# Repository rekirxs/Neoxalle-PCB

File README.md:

# NeoXalle-PCB

A full PCB work for a sport sensorial reaction device called NeoXalle.

The function of this pcb is to be the main board to control the whole system of the multisensorial output and input, such as a motor vibrator and led ring, this includes a Esp32c3 to connect thru ESP-NOW to the master that connects to the mobile app, down below theres a video showing off the prototype and its function with a table tennis practice.

**Overview**

This repository contains the design files and the images of each part.

### [Watch this video on YouTube](https://youtu.be/leAVq9ZJ1fE)
**Screenshots**

Onshape: https://cad.onshape.com/documents/914ab1e3f9de5857bd04cad5/w/fe3775e11ed4b5ce7c2d1721/e/2a4a9405b78e8a972a361091?renderMode=0&uiState=6a0a02086fff7314551b3a2c

|Item                        |Description                        |Quantity|Unit Price ($)|Total Price ($)|URL                                                 |Running Total|
|----------------------------|-----------------------------------|--------|--------------|---------------|----------------------------------------------------|-------------|
|ESP32-C3 Super Mini         |Microcontroller                    |1       |3.48          |3.48           |https://es.aliexpress.com/item/1005007941259180.html|3.48         |
|MPU6050                     | Acelerometer                      |1       |2.47          |2.47           |https://es.aliexpress.com/item/1005008796700745.html|5.95         |
|Pogo Pins                   |4 pin 360 Degree Magnetic Pogo Pins|1       |4.3           |4.3            |https://es.aliexpress.com/item/1005007457425590.html|10.25        |
|1200mAh battery             |Battery                            |1       |24.59         |24.59          |https://es.aliexpress.com/item/1005011601135401.html|34.84        |
|Coin Vibrator Motor         |Vibrator Motor                     |1       |1.22          |1.22           |https://es.aliexpress.com/item/1005006713206227.html|36.06        |
|24x LED Ring WS2812b        |LED Ring                           |1       |2.24          |2.24           |https://es.aliexpress.com/item/1005009290613680.html|38.3         |
|12v-5v Buck Converter       |Buck Converter                     |1       |3.04          |3.04           |https://es.aliexpress.com/item/1005008257960729.html|41.34        |
|2n39004 Transistor          |Transistor                         |1       |4.1           |4.1            |https://es.aliexpress.com/item/1005004029392929.html|45.44        |
|1N4007 Diode                |Schockty Diode                     |1       |1.75          |1.75           |https://es.aliexpress.com/item/1005007807556976.html|47.19        |
|680ohm resistor             |Resistor                           |1       |1.33          |1.33           |https://es.aliexpress.com/item/32847423196.html     |48.52        |
|AMS1117                     |Voltage Reductor                   |1       |1.34          |1.34           |https://es.aliexpress.com/item/4001091314348.html   |49.86        |
|USB-C Battery Charger Module|Battery Charger Module             |1       |1.1           |1.1            |https://es.aliexpress.com/item/1005006161180492.html|50.96        |

**Repository layout**
- `cad/` — CAD files and case models
- `pcb/` — KiCad schematic and PCB files- `firmware/` — KMK firmware and `keymap.py`
- `images/` — project screenshots used by this README

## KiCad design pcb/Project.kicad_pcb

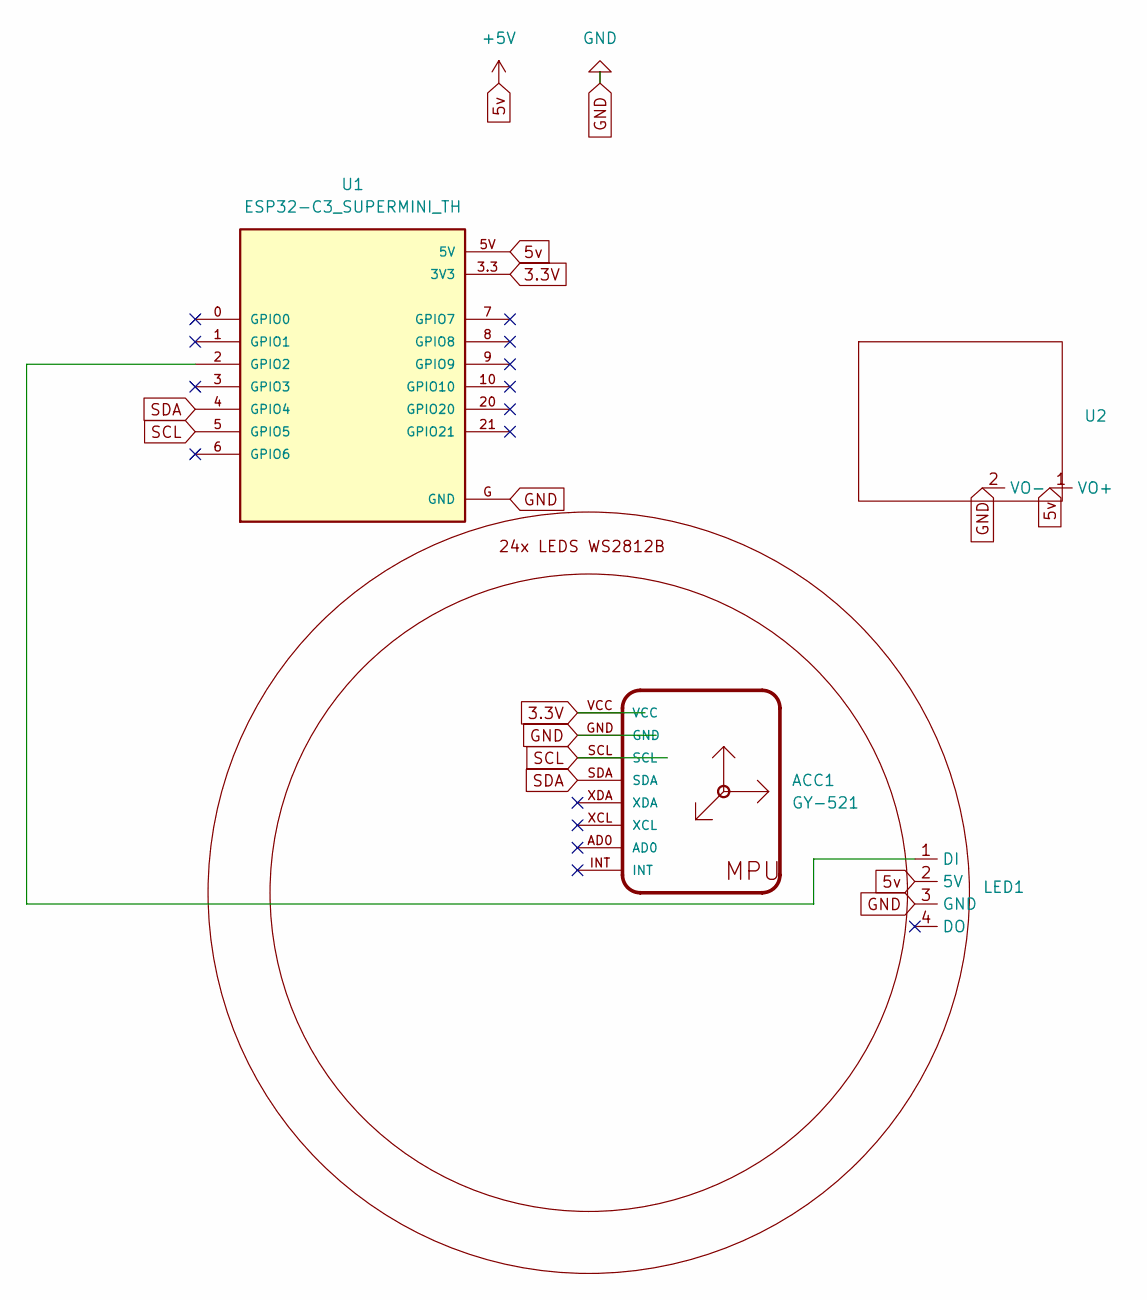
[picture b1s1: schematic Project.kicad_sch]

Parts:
ACC1: GY-521
LED1: Untitled
U1: ESP32-C3_SUPERMINI_TH; MODULE_ESP32-C3_SUPERMINI_TH
U2: ModuleCharger

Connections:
3.3V: ACC1.VCC, U1.3.3 (3V3)
5v: LED1.2 (5V), U1.5V, U2.1 (VO+)
GND: ACC1.GND, LED1.3 (GND), U1.G (GND), U2.2 (VO-)
unnamed: LED1.1 (DI), U1.2 (GPIO2)
SCL: ACC1.SCL, U1.5 (GPIO5)
SDA: ACC1.SDA, U1.4 (GPIO4)

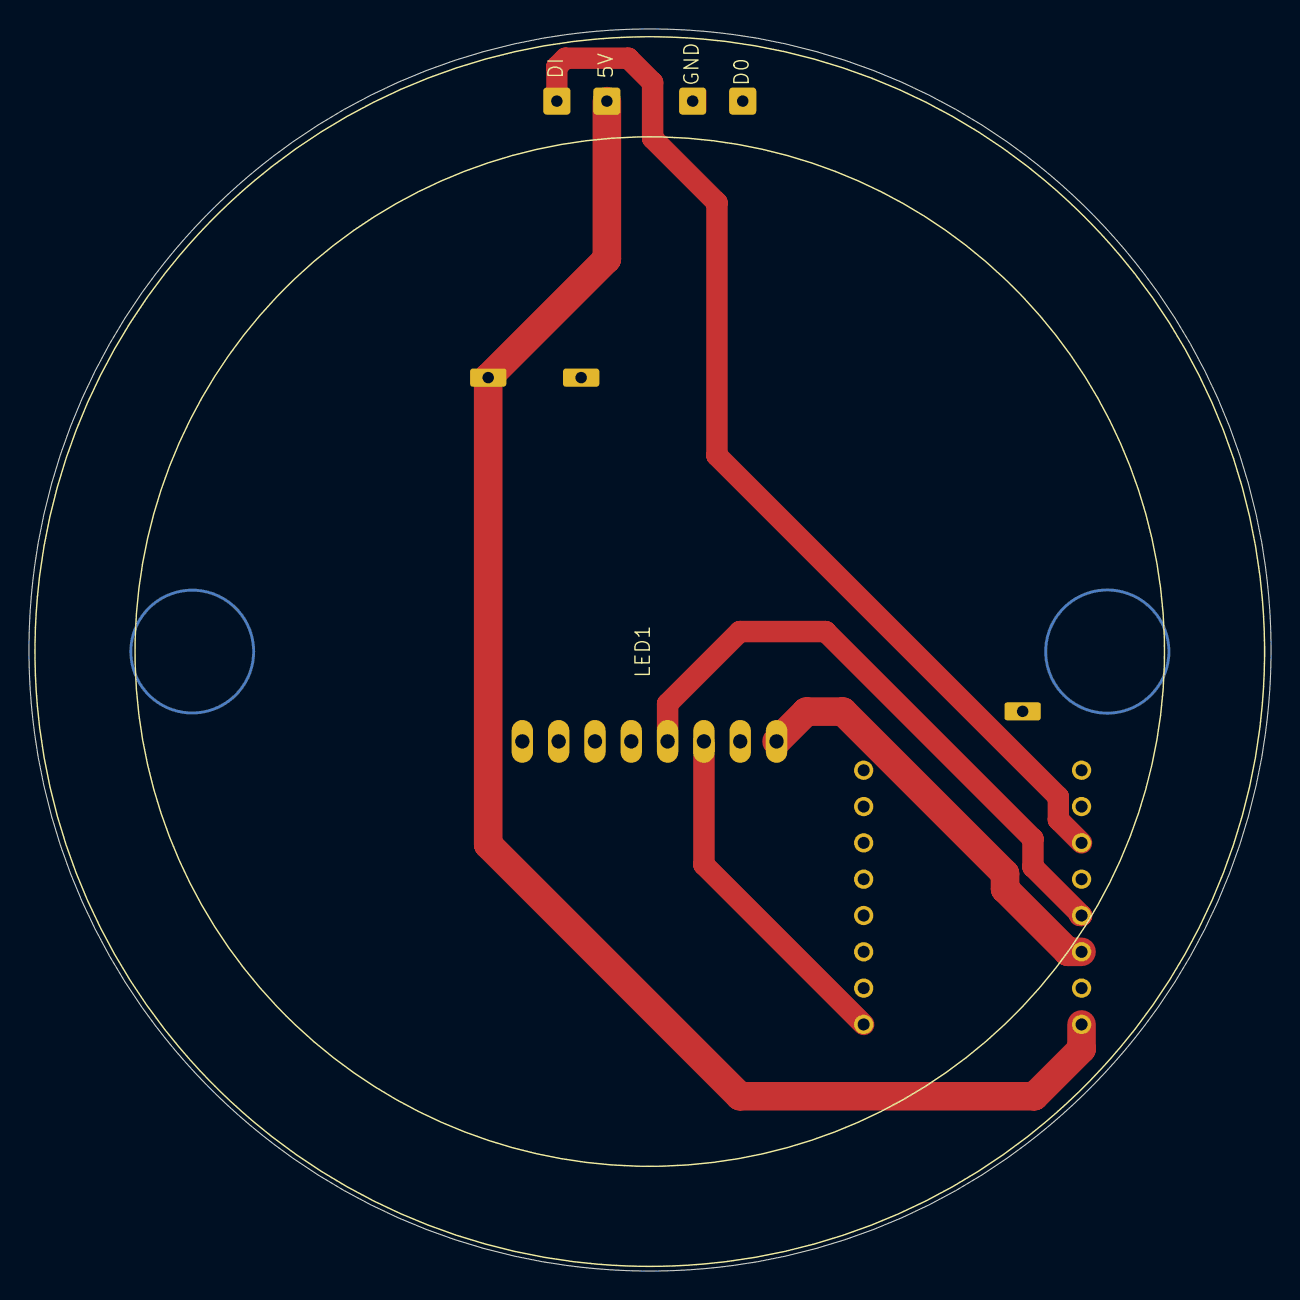
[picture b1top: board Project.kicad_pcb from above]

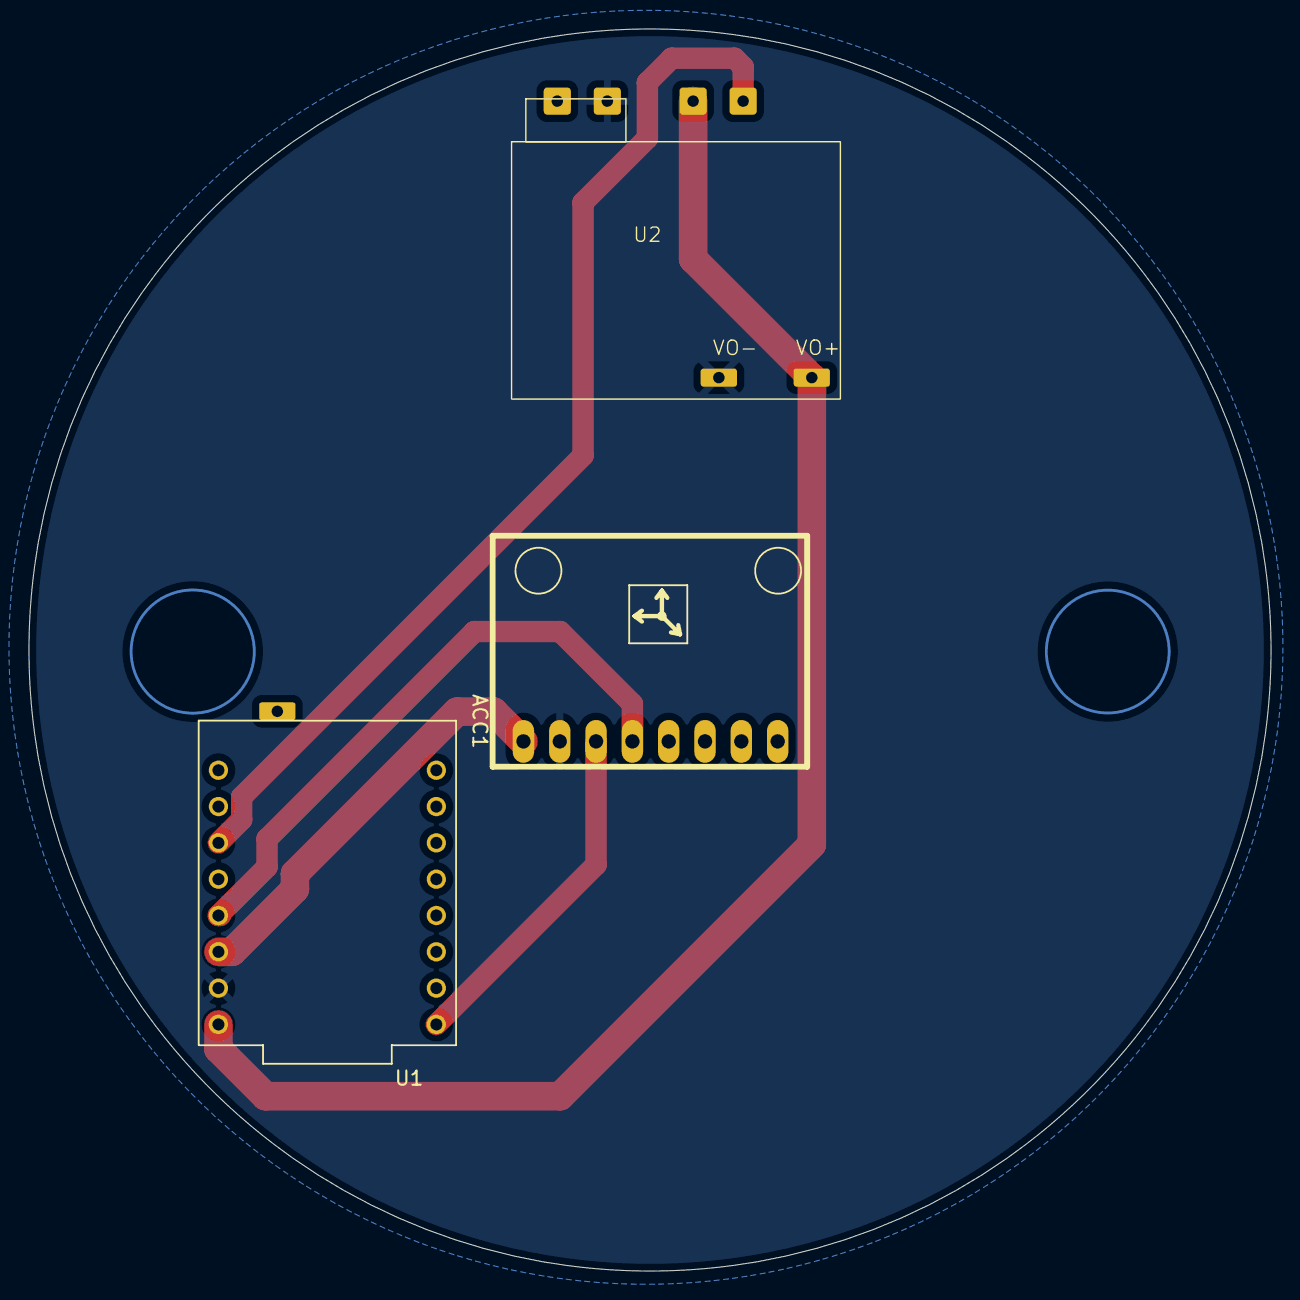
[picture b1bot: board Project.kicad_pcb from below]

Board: 2 copper layers, 86.9 x 86.9 mm, 4 parts (3 on the bottom side), 6 nets.

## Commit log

2026-03-21 Create files
2026-03-22 Revise README for NeoXalle-PCB project
    Updated project name and added detailed information about the NeoXalle-PCB, including an overview, screenshots, BOM, and repository layout.
2026-03-22 Revise BOM and repository layout in README
    Updated the Bill of Materials (BOM) with additional components and corrected formatting in the repository layout section.
2026-03-22 Add YouTube video link and thumbnail to README
    Added a video link and thumbnail to the README.
2026-03-31 Refactor item list to table format in README
    Updated item list format in README with a table layout for better readability.
2026-03-31 Remove duplicate video link in README.md
2026-05-17 Add Onshape link and update item description table
    Added Onshape document link and updated item table.
2026-05-21 Enhance README with PCB function details
    Added detailed description of the PCB's function and components.
